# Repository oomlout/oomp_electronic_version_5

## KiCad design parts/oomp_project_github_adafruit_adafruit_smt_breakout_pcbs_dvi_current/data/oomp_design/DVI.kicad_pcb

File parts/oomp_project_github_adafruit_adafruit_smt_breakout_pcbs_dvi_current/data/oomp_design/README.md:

# OOMP KiCad design copy

Open `DVI.kicad_pro` (or the `.kicad_pcb` / `.kicad_sch`) in KiCad. Local OOMP libraries are under `libraries/`. Original inputs are preserved in [../original/](../original/).

Only verified unchanged installed KiCad defaults were renamed. Modified, custom, unmatched and unavailable items remain unchanged. Soldering variants are never swapped during conversion. Existing pad coordinates, nets and UUIDs are preserved.

See [conversion_report.yaml](conversion_report.yaml) for every conversion and skip. Copy this directory before editing; regeneration refuses to overwrite edited design files.

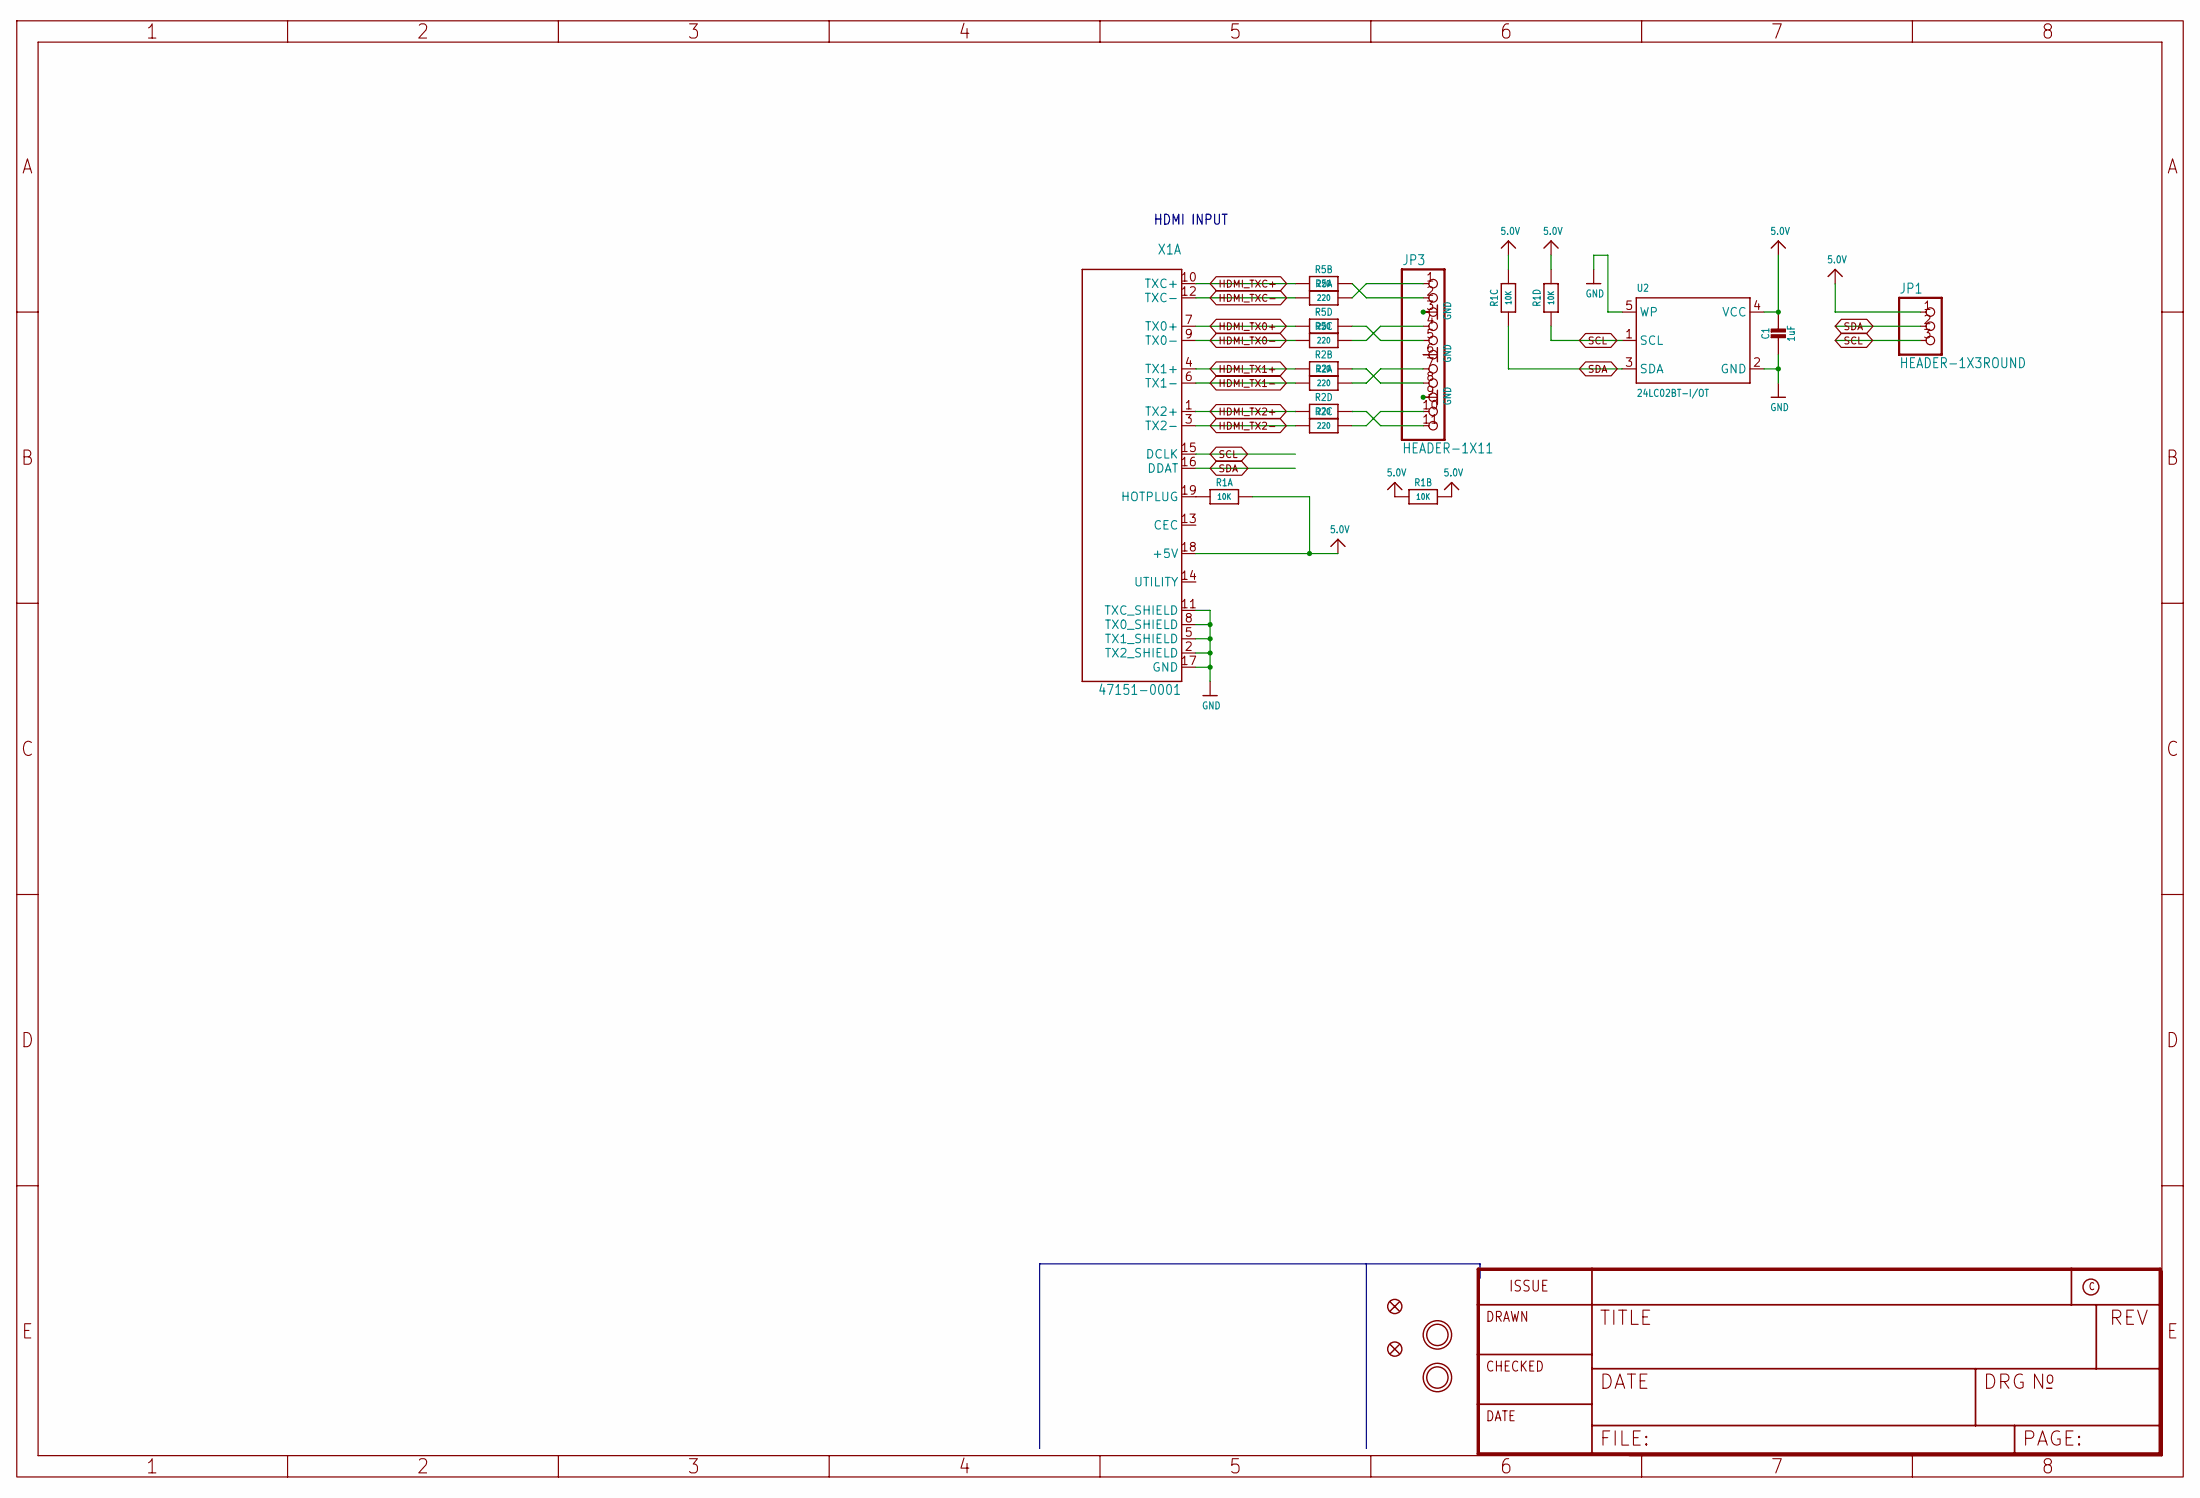
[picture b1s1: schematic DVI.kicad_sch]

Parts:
C1: 1uF; 0603-NO
FID1, FID2: FIDUCIAL_1MM
JP1: HEADER-1X3ROUND; 1X03_ROUND
JP3: HEADER-1X11; 1X11_ROUND
R1: 10K; RESPACK_4X0603
R2, R5: 220; RESPACK_4X0603
U2: 24LC02BT-I/OT; SOT23-5
U$32, U$33: MOUNTINGHOLE2.5; MOUNTINGHOLE_2.5_PLATED
X1: 47151-0001; HDMI_MOLEX_47151-0001

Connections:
5.0V: C1.1, JP1.1, R1.2 (1), R1.5 (2), R1.6 (2), R1.7 (2), R1.8 (2), U2.4 (VCC), X1.18 (+5V)
GND: C1.2, JP3.3, JP3.6, JP3.9, U2.2 (GND), U2.5 (WP), X1.2 (TX2_SHIELD), X1.5 (TX1_SHIELD), X1.8 (TX0_SHIELD), X1.11 (TXC_SHIELD), X1.17 (GND), X1.P$1 (GND), X1.P$2 (GND), X1.P$3 (GND), X1.P$4 (GND)
HDMI_TX0+: R5.4 (1), X1.7 (TX0+)
HDMI_TX0-: R5.3 (1), X1.9 (TX0-)
HDMI_TX1+: R2.2 (1), X1.4 (TX1+)
HDMI_TX1-: R2.1, X1.6 (TX1-)
HDMI_TX2+: R2.4 (1), X1.1 (TX2+)
HDMI_TX2-: R2.3 (1), X1.3 (TX2-)
HDMI_TXC+: R5.2 (1), X1.10 (TXC+)
HDMI_TXC-: R5.1, X1.12 (TXC-)
unnamed: R1.1, X1.19 (HOTPLUG)
SCL: JP1.3, R1.4 (1), U2.1 (SCL), X1.15 (DCLK)
SDA: JP1.2, R1.3 (1), U2.3 (SDA), X1.16 (DDAT)
TX0+: JP3.5, R5.5 (2)
TX0-: JP3.4, R5.6 (2)
TX1+: JP3.8, R2.7 (2)
TX1-: JP3.7, R2.8 (2)
TX2+: JP3.11, R2.5 (2)
TX2-: JP3.10, R2.6 (2)
TXC+: JP3.2, R5.7 (2)
TXC-: JP3.1, R5.8 (2)

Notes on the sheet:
HDMI INPUT

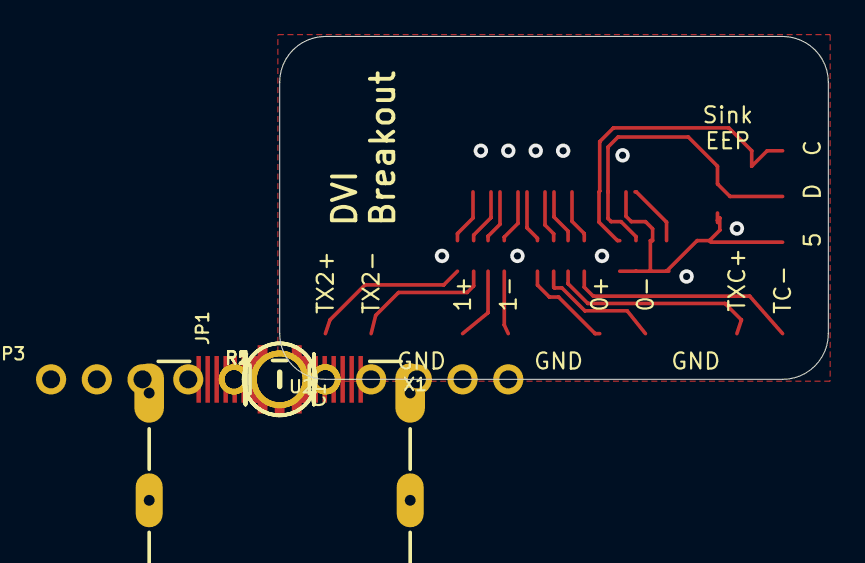
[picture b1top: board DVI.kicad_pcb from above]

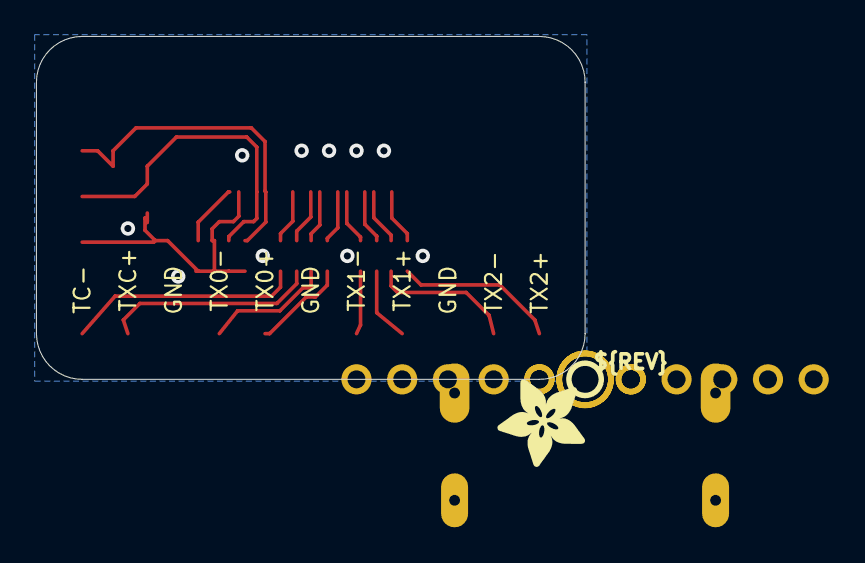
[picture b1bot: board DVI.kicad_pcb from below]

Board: 2 copper layers, 30.5 x 19.1 mm, 14 parts (2 on the bottom side), 21 nets.

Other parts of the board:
U$6: ADAFRUIT_5MM
U$73: PCBFEAT-REV-040

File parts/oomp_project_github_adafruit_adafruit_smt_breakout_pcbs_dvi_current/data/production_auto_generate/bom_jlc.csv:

Comment,Designator,Footprint,LCSC Part #
,JP1,DVI-import-fps:1X03_ROUND,C49257
,JP3,DVI-import-fps:1X11_ROUND,C2894934
,U$6,DVI-import-fps:ADAFRUIT_5MM,
,U$73,DVI-import-fps:PCBFEAT-REV-040,
10K,R1,DVI-import-fps:RESPACK_4X0603,C98220
1uF,C1,DVI-import-fps:0603-NO,C5673
220,"R2,R5",DVI-import-fps:RESPACK_4X0603,C2907127
24LC02BT-I/OT,U2,DVI-import-fps:SOT23-5,
47151-0001,X1,DVI-import-fps:HDMI_MOLEX_47151-0001,

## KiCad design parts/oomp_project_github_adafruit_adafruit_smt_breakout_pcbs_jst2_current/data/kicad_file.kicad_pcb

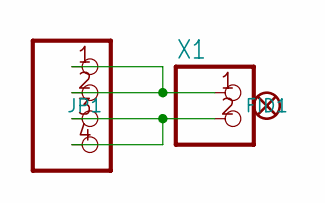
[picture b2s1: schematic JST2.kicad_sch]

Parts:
FID1: FIDUCIAL""; FIDUCIAL_1MM
JP1: PADS-4
X1: CON_JST_PH_2PIN; JSTPH2

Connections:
unnamed: JP1.1, JP1.2, X1.1
unnamed: JP1.3, JP1.4, X1.2

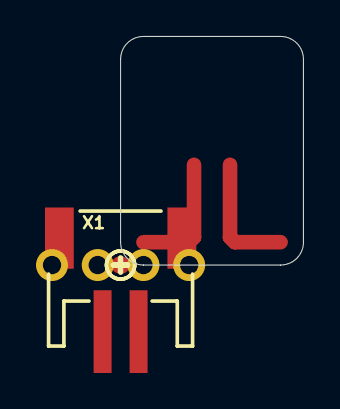
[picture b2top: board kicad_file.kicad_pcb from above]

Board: 2 copper layers, 10.2 x 12.7 mm, 6 parts (1 on the bottom side), 2 nets.

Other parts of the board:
U$1: SYMBOL_PLUS
U$2: SYMBOL_MINUS
U$4: ADAFRUIT_3.5MM

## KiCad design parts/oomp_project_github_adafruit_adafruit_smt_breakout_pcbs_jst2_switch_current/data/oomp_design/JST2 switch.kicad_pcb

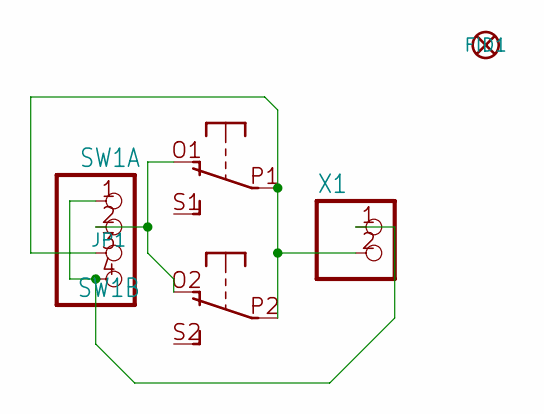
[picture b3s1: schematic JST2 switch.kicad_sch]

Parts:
FID1: FIDUCIAL""; FIDUCIAL_1MM
JP1: PADS-4
SW1: DPDT-EG1390; EG1390
X1: CON_JST_PH_2PIN; JSTPH2

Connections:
GND: JP1.1, JP1.4, X1.1
unnamed: JP1.3, SW1.P1, SW1.P2, X1.2
unnamed: JP1.2, SW1.O1 (O), SW1.O2 (O)

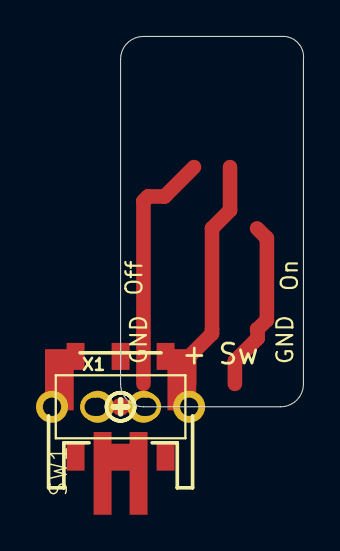
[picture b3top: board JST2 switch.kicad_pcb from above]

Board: 2 copper layers, 10.2 x 20.6 mm, 7 parts (1 on the bottom side), 3 nets.

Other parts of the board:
U$1: SYMBOL_PLUS
U$2: SYMBOL_MINUS
U$3: ADAFRUIT_5MM

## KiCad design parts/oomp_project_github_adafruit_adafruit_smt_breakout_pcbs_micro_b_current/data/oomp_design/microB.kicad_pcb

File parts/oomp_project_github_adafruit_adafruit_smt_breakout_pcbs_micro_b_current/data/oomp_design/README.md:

# OOMP KiCad design copy

Open `microB.kicad_pro` (or the `.kicad_pcb` / `.kicad_sch`) in KiCad. Local OOMP libraries are under `libraries/`. Original inputs are preserved in [../original/](../original/).

Only verified unchanged installed KiCad defaults were renamed. Modified, custom, unmatched and unavailable items remain unchanged. Soldering variants are never swapped during conversion. Existing pad coordinates, nets and UUIDs are preserved.

See [conversion_report.yaml](conversion_report.yaml) for every conversion and skip. Copy this directory before editing; regeneration refuses to overwrite edited design files.

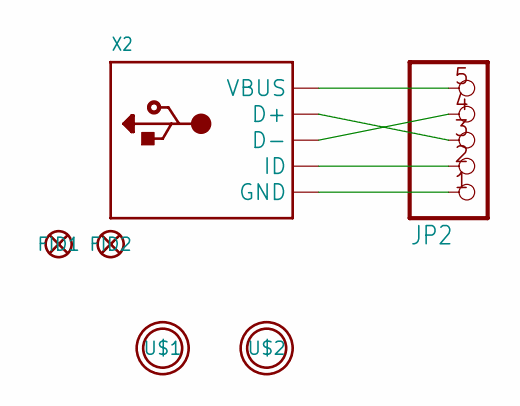
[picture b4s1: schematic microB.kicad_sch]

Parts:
FID1, FID2: FIDUCIAL""; FIDUCIAL_1MM
JP2: HEADER-1X570MIL; 1X05_ROUND_70
U$1, U$2: MOUNTINGHOLE2.5; MOUNTINGHOLE_2.5_PLATED
X2: USBMICRO_20329; 4UCONN_20329

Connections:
D+: JP2.3, X2.D+
D-: JP2.4, X2.D-
GND: JP2.1, X2.BASE@1 (GND), X2.BASE@2 (GND), X2.GND, X2.SPRT@1 (GND), X2.SPRT@2 (GND), X2.SPRT@3 (GND), X2.SPRT@4 (GND)
ID: JP2.2, X2.ID
VBUS: JP2.5, X2.VBUS

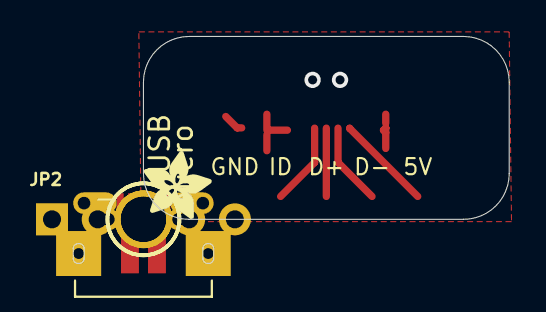
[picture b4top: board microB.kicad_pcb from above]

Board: 2 copper layers, 20.3 x 10.2 mm, 7 parts (0 on the bottom side), 5 nets.

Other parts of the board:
U$4: ADAFRUIT_3.5MM
